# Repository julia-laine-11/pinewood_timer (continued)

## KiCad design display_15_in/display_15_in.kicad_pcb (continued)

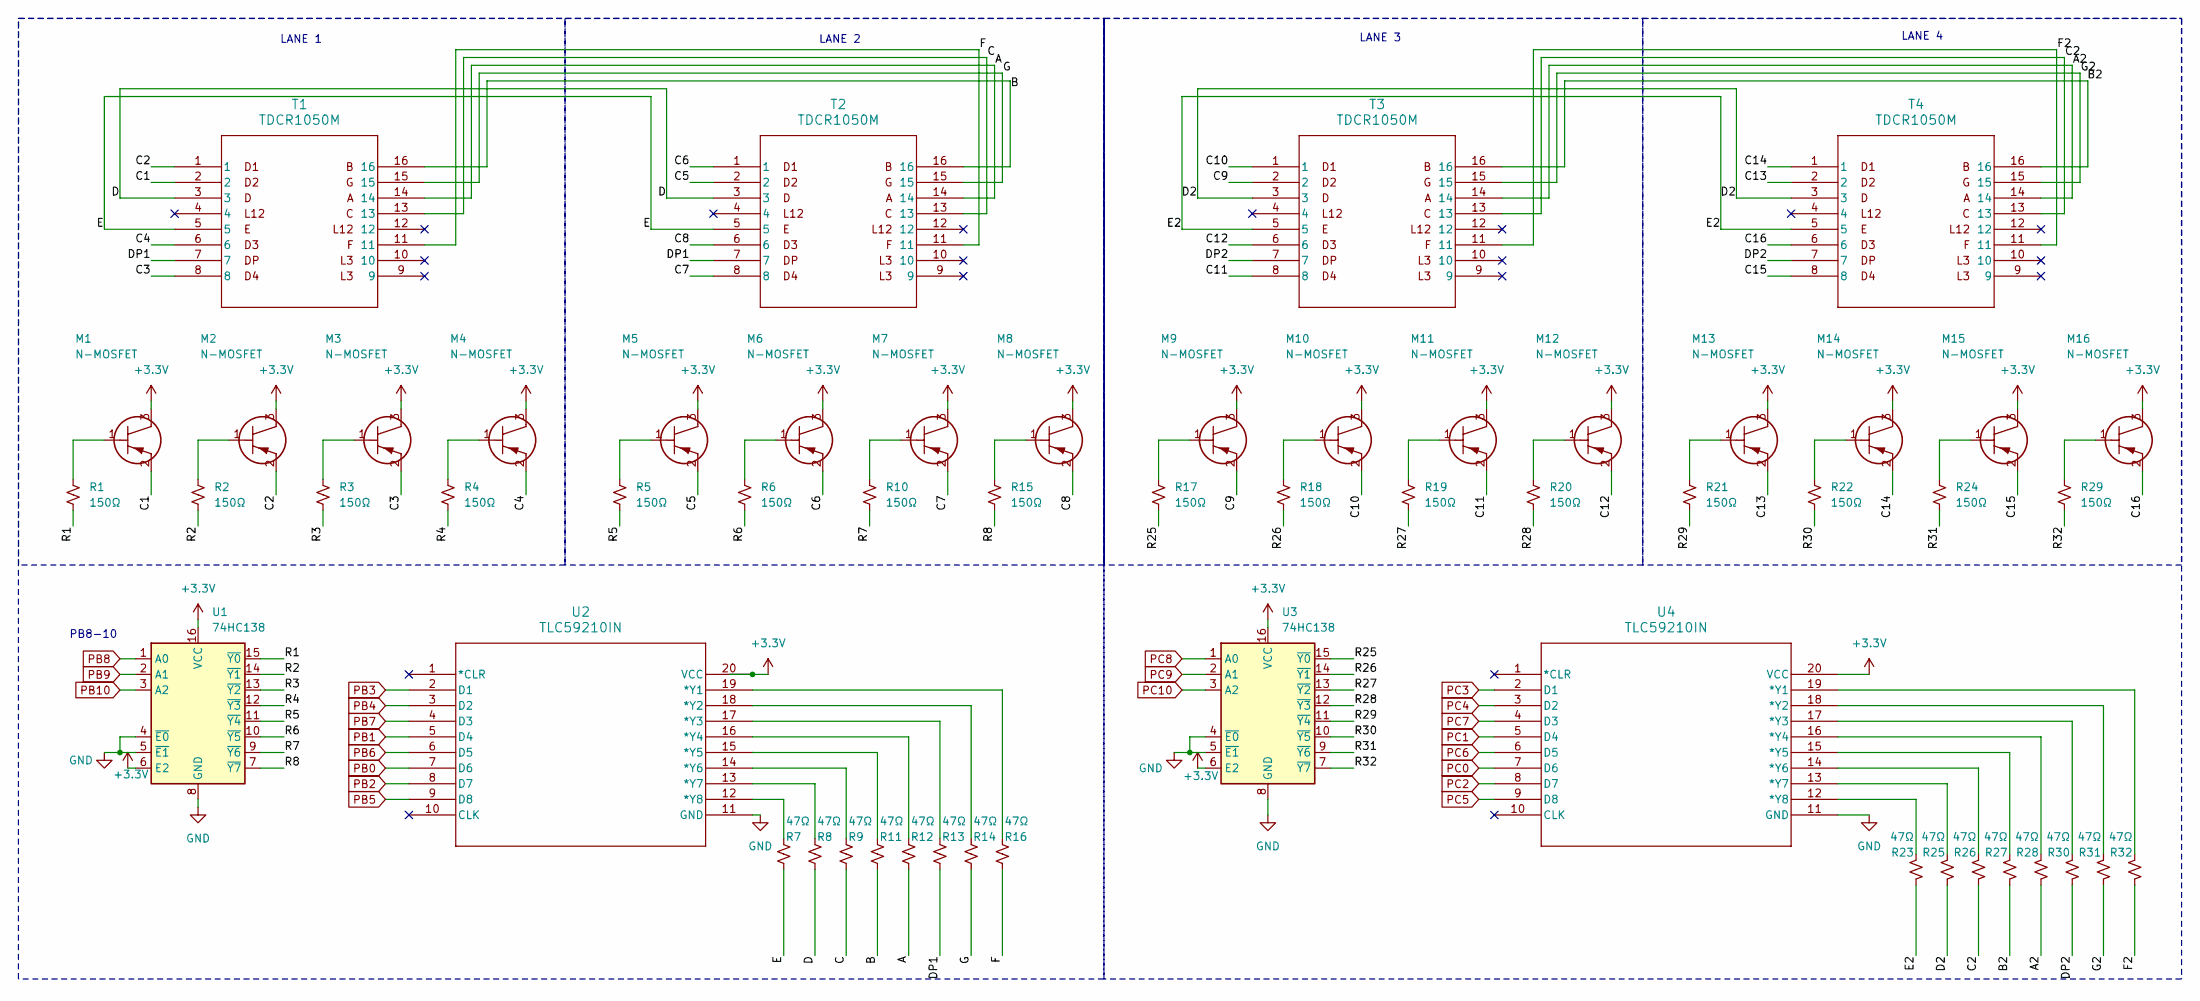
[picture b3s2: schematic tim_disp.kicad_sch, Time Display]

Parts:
M1, M2, M3, M4, M5, M6, M7, M8, M9, M10, M11, M12, M13, M14, M15, M16: N-MOSFET; TO-236AB_SOT23_NEX
R1, R2, R3, R4, R5, R6, R10, R15, R17, R18, R19, R20, R21, R22, R24, R29: 150Ω; R_0805_2012Metric
R7, R8, R9, R11, R12, R13, R14, R16, R23, R25, R26, R27, R28, R30, R31, R32: 47Ω; R_0805_2012Metric
T1, T2, T3, T4: TDCR1050M; TDCG1060M_VIS
U1, U3: 74HC138; SOIC127P600X175-16N
U2, U4: TLC59210IN; SOP65P640X120-20N

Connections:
+3.3V: M1.3, M2.3, M3.3, M4.3, M5.3, M6.3, M7.3, M8.3, M9.3, M10.3, M11.3, M12.3, M13.3, M14.3, M15.3, M16.3, U1.6 (E2), U1.16 (VCC), U2.20 (VCC), U3.6 (E2), U3.16 (VCC), U4.20 (VCC); also elsewhere on the board
/tim_disp/A: R12.2, T1.14, T2.14
/tim_disp/A2: R28.2, T3.14, T4.14
/tim_disp/B: R11.2, T1.16, T2.16
/tim_disp/B2: R27.2, T3.16, T4.16
/tim_disp/C: R9.2, T1.13, T2.13
/tim_disp/C1: M1.2, T1.2
/tim_disp/C2: M2.2, R26.2, T1.1, T3.13, T4.13
/tim_disp/C3: M3.2, T1.8
/tim_disp/C4: M4.2, T1.6
/tim_disp/C5: M5.2, T2.2
/tim_disp/C6: M6.2, T2.1
/tim_disp/C7: M7.2, T2.8
/tim_disp/C8: M8.2, T2.6
/tim_disp/C9: M9.2, T3.2
/tim_disp/C10: M10.2, T3.1
/tim_disp/C11: M11.2, T3.8
/tim_disp/C12: M12.2, T3.6
/tim_disp/C13: M13.2, T4.2
/tim_disp/C14: M14.2, T4.1
/tim_disp/C15: M15.2, T4.8
/tim_disp/C16: M16.2, T4.6
/tim_disp/D: R8.2, T1.3, T2.3
/tim_disp/D2: R25.2, T3.3, T4.3
/tim_disp/DP1: R13.2, T1.7, T2.7
/tim_disp/DP2: R30.2, T3.7, T4.7
/tim_disp/E: R7.2, T1.5, T2.5
/tim_disp/E2: R23.2, T3.5, T4.5
/tim_disp/F: R16.2, T1.11, T2.11
/tim_disp/F2: R32.2, T3.11, T4.11
/tim_disp/G: R14.2, T1.15, T2.15
/tim_disp/G2: R31.2, T3.15, T4.15
/tim_disp/R1: R1.2, U1.15 (~Y0)
/tim_disp/R2: R2.2, U1.14 (~Y1)
/tim_disp/R3: R3.2, U1.13 (~Y2)
/tim_disp/R4: R4.2, U1.12 (~Y3)
/tim_disp/R5: R5.2, U1.11 (~Y4)
/tim_disp/R6: R6.2, U1.10 (~Y5)
/tim_disp/R7: R10.2, U1.9 (~Y6)
/tim_disp/R8: R15.2, U1.7 (~Y7)
/tim_disp/R25: R17.2, U3.15 (~Y0)
/tim_disp/R26: R18.2, U3.14 (~Y1)
/tim_disp/R27: R19.2, U3.13 (~Y2)
/tim_disp/R28: R20.2, U3.12 (~Y3)
/tim_disp/R29: R21.2, U3.11 (~Y4)
/tim_disp/R30: R22.2, U3.10 (~Y5)
/tim_disp/R31: R24.2, U3.9 (~Y6)
/tim_disp/R32: R29.2, U3.7 (~Y7)
GND: U1.4 (~E0), U1.5 (~E1), U1.8 (GND), U2.11 (GND), U3.4 (~E0), U3.5 (~E1), U3.8 (GND), U4.11 (GND); also elsewhere on the board
unnamed: M1.1, R1.1
unnamed: M2.1, R2.1
unnamed: M3.1, R3.1
unnamed: M4.1, R4.1
unnamed: M5.1, R5.1
unnamed: M6.1, R6.1
unnamed: M7.1, R10.1
unnamed: M8.1, R15.1
unnamed: M9.1, R17.1
unnamed: M10.1, R18.1
unnamed: M11.1, R19.1
unnamed: M12.1, R20.1
unnamed: M13.1, R21.1
unnamed: M14.1, R22.1
unnamed: M15.1, R24.1
unnamed: M16.1, R29.1
unnamed: R16.1, U2.19 (*Y1)
unnamed: R14.1, U2.18 (*Y2)
unnamed: R13.1, U2.17 (*Y3)
unnamed: R12.1, U2.16 (*Y4)
unnamed: R11.1, U2.15 (*Y5)
unnamed: R9.1, U2.14 (*Y6)
unnamed: R8.1, U2.13 (*Y7)
unnamed: R7.1, U2.12 (*Y8)
unnamed: R32.1, U4.19 (*Y1)
unnamed: R31.1, U4.18 (*Y2)
unnamed: R30.1, U4.17 (*Y3)
unnamed: R28.1, U4.16 (*Y4)
unnamed: R27.1, U4.15 (*Y5)
unnamed: R26.1, U4.14 (*Y6)
unnamed: R25.1, U4.13 (*Y7)
unnamed: R23.1, U4.12 (*Y8)
PB0: U2.7 (D6); also elsewhere on the board
PB1: U2.5 (D4); also elsewhere on the board
PB2: U2.8 (D7); also elsewhere on the board
PB3: U2.2 (D1); also elsewhere on the board
PB4: U2.3 (D2); also elsewhere on the board
PB5: U2.9 (D8); also elsewhere on the board
PB6: U2.6 (D5); also elsewhere on the board
PB7: U2.4 (D3); also elsewhere on the board
PB8: U1.1 (A0); also elsewhere on the board
PB9: U1.2 (A1); also elsewhere on the board
PB10: U1.3 (A2); also elsewhere on the board
PC0: U4.7 (D6); also elsewhere on the board
PC1: U4.5 (D4); also elsewhere on the board
PC2: U4.8 (D7); also elsewhere on the board
PC3: U4.2 (D1); also elsewhere on the board
PC4: U4.3 (D2); also elsewhere on the board
PC5: U4.9 (D8); also elsewhere on the board
PC6: U4.6 (D5); also elsewhere on the board
PC7: U4.4 (D3); also elsewhere on the board
PC8: U3.1 (A0); also elsewhere on the board
PC9: U3.2 (A1); also elsewhere on the board
PC10: U3.3 (A2); also elsewhere on the board

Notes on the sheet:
LANE 4
LANE 2
PB8-10
LANE 1
LANE 3

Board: 2 copper layers, 78 parts (0 on the bottom side), 126 nets, no tracks yet.

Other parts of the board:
J1: 559592430; CONN24_559592430_MOL
PT1, PT2, PT3, PT4: LED_D5.0mm
R41, R42, R43, R44: 56KΩ; R_0805_2012Metric
U9: S16B-PHDSSLFSN; S16B-PHDSSLFSN_JST

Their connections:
+3.3V: J1.23, PT1.1 (+), PT2.1 (+), PT3.1 (+), PT4.1 (+); also elsewhere on the board
GND: J1.24, R41.2, R42.2, R43.2, R44.2; also elsewhere on the board
PA0: U9.1; also elsewhere on the board
PA1: U9.2; also elsewhere on the board
PA2: U9.3; also elsewhere on the board
PA3: U9.4; also elsewhere on the board
PA4: U9.5; also elsewhere on the board
PA5: U9.6; also elsewhere on the board
PA6: U9.7; also elsewhere on the board
PA7: U9.8; also elsewhere on the board
PA8: U9.9; also elsewhere on the board
PA9: U9.10; also elsewhere on the board
PA10: U9.11; also elsewhere on the board
PA11: PT1.2 (-), R41.1, U9.12
PA12: PT2.2 (-), R42.1, U9.13
PA13: PT3.2 (-), R43.1, U9.14
PA14: PT4.2 (-), R44.1, U9.15
PB0: J1.1; also elsewhere on the board
PB1: J1.2; also elsewhere on the board
PB2: J1.3; also elsewhere on the board
PB3: J1.4; also elsewhere on the board
PB4: J1.5; also elsewhere on the board
PB5: J1.6; also elsewhere on the board
PB6: J1.7; also elsewhere on the board
PB7: J1.8; also elsewhere on the board
PB8: J1.9; also elsewhere on the board
PB9: J1.10; also elsewhere on the board
PB10: J1.11; also elsewhere on the board
PC0: J1.12; also elsewhere on the board
PC1: J1.13; also elsewhere on the board
PC2: J1.14; also elsewhere on the board
PC3: J1.15; also elsewhere on the board
PC4: J1.16; also elsewhere on the board
PC5: J1.17; also elsewhere on the board
PC6: J1.18; also elsewhere on the board
PC7: J1.19; also elsewhere on the board
PC8: J1.20; also elsewhere on the board
PC9: J1.21; also elsewhere on the board
PC10: J1.22; also elsewhere on the board

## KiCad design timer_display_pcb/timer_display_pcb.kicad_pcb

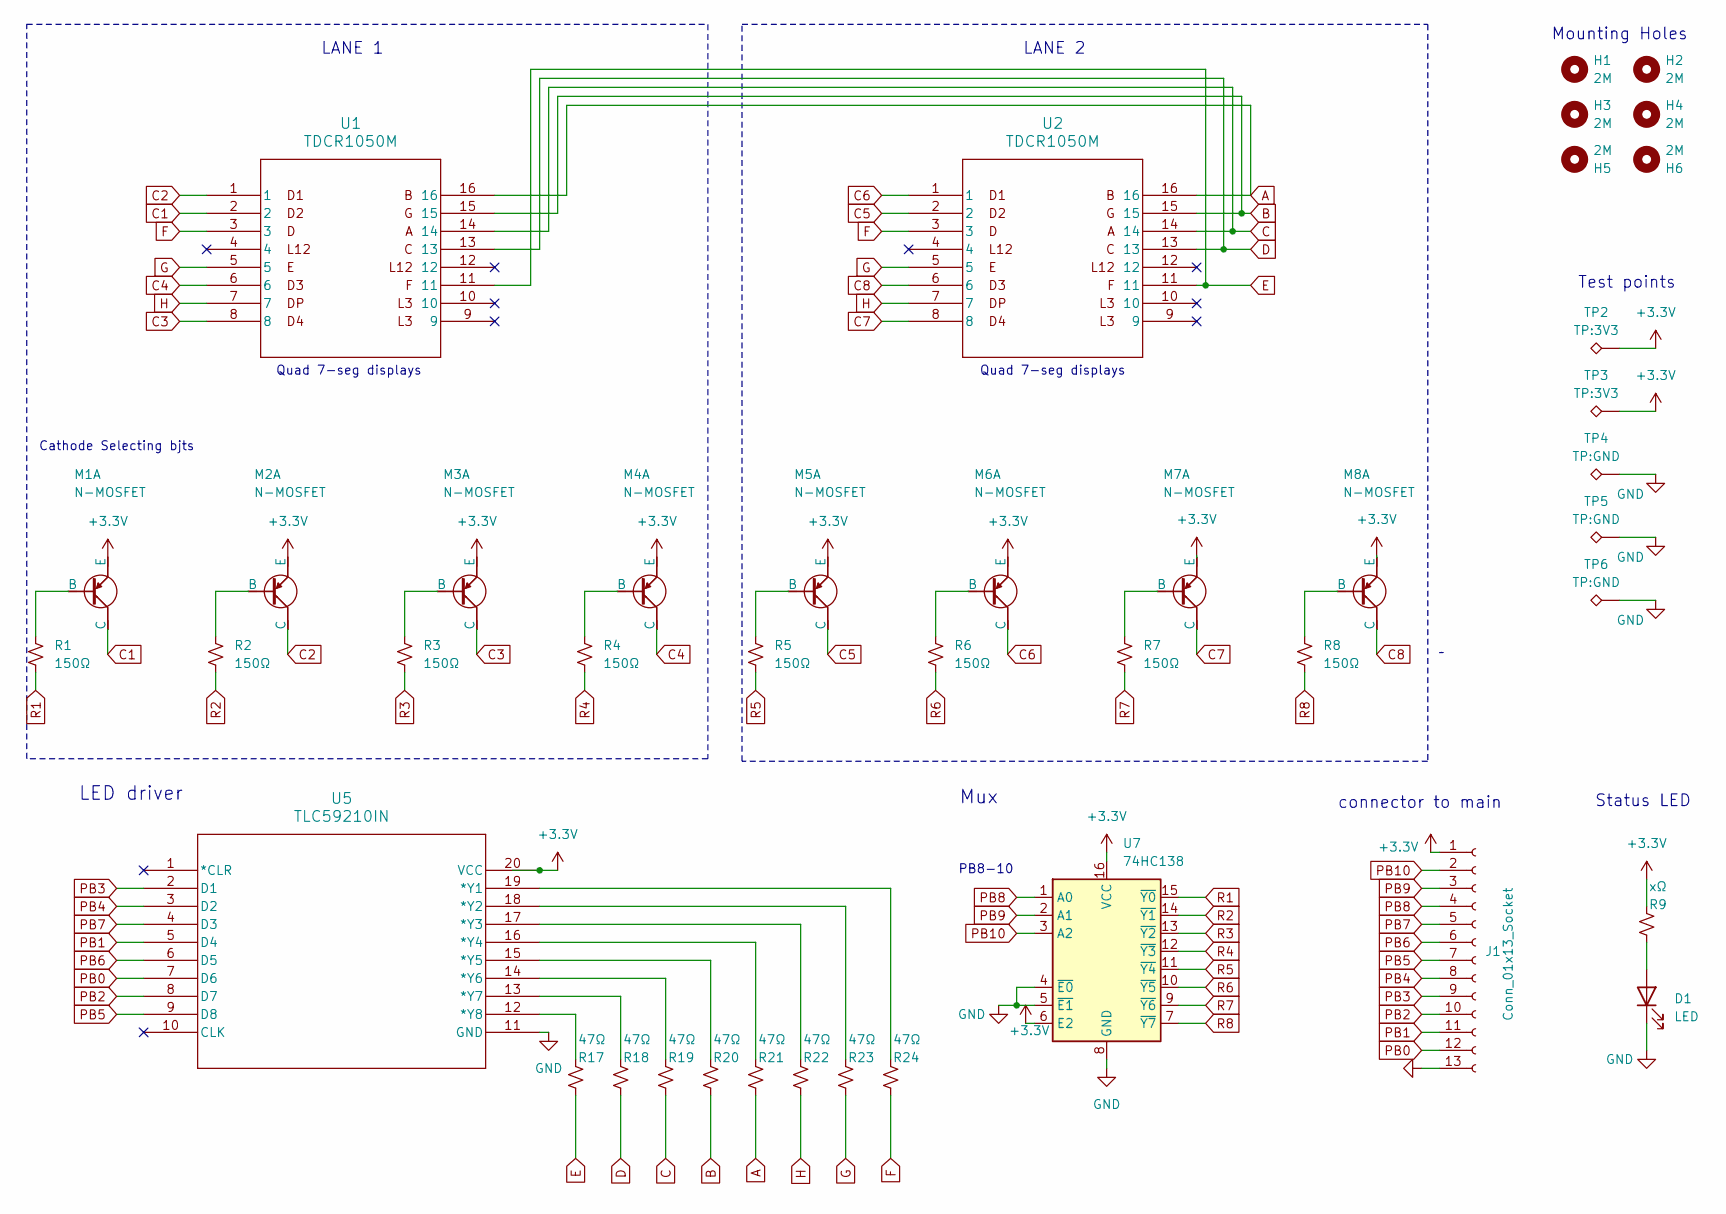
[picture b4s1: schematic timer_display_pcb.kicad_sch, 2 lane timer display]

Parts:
D1: LED; LED_0805_2012Metric
H1, H2, H3, H4, H5, H6: 2M; MountingHole_4.3mm_M4
J1: Conn_01x13_Socket; JST_EH_S13B-EH_1x13_P2.50mm_Horizontal
M1, M2, M3, M4, M5, M6, M7, M8: N-MOSFET; TO-236AB_SOT23_NEX
R1, R2, R3, R4, R5, R6, R7, R8: 150Ω; R_0805_2012Metric_Pad1.20x1.40mm_HandSolder
R9: xΩ; R_0805_2012Metric_Pad1.20x1.40mm_HandSolder
R17, R18, R19, R20, R21, R22, R23, R24: 47Ω; R_0805_2012Metric_Pad1.20x1.40mm_HandSolder
TP2, TP3: TP:3V3; TestPoint_Pad_2.0x2.0mm
TP4, TP5, TP6: TP:GND; TestPoint_Pad_2.0x2.0mm
U1, U2: TDCR1050M; TDCG1060M_VIS
U5: TLC59210IN; SOP65P640X120-20N
U7: 74HC138; SOIC127P600X175-16N

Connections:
+3.3V: J1.1, M1.1 (E), M2.1 (E), M3.1 (E), M4.1 (E), M5.1 (E), M6.1 (E), M7.1 (E), M8.1 (E), R9.1, TP2.1, TP3.1, U5.20 (VCC), U7.6 (E2), U7.16 (VCC)
A: R21.2, U1.16, U2.16
B: R20.2, U1.15, U2.15
C: R19.2, U1.14, U2.14
C1: M1.3 (C), U1.2
C2: M2.3 (C), U1.1
C3: M3.3 (C), U1.8
C4: M4.3 (C), U1.6
C5: M5.3 (C), U2.2
C6: M6.3 (C), U2.1
C7: M7.3 (C), U2.8
C8: M8.3 (C), U2.6
D: R18.2, U1.13, U2.13
E: R17.2, U1.11, U2.11
F: R24.2, U1.3, U2.3
G: R23.2, U1.5, U2.5
GND: D1.1 (K), J1.13, TP4.1, TP5.1, TP6.1, U5.11 (GND), U7.4 (~E0), U7.5 (~E1), U7.8 (GND)
H: R22.2, U1.7, U2.7
unnamed: D1.2 (A), R9.2
unnamed: M1.2 (B), R1.1
unnamed: M2.2 (B), R2.1
unnamed: M3.2 (B), R3.1
unnamed: M4.2 (B), R4.1
unnamed: M5.2 (B), R5.1
unnamed: M6.2 (B), R6.1
unnamed: M7.2 (B), R7.1
unnamed: M8.2 (B), R8.1
unnamed: R24.1, U5.19 (*Y1)
unnamed: R23.1, U5.18 (*Y2)
unnamed: R22.1, U5.17 (*Y3)
unnamed: R21.1, U5.16 (*Y4)
unnamed: R20.1, U5.15 (*Y5)
unnamed: R19.1, U5.14 (*Y6)
unnamed: R18.1, U5.13 (*Y7)
unnamed: R17.1, U5.12 (*Y8)
PB0: J1.12, U5.7 (D6)
PB1: J1.11, U5.5 (D4)
PB2: J1.10, U5.8 (D7)
PB3: J1.9, U5.2 (D1)
PB4: J1.8, U5.3 (D2)
PB5: J1.7, U5.9 (D8)
PB6: J1.6, U5.6 (D5)
PB7: J1.5, U5.4 (D3)
PB8: J1.4, U7.1 (A0)
PB9: J1.3, U7.2 (A1)
PB10: J1.2, U7.3 (A2)
R1: R1.2, U7.15 (~Y0)
R2: R2.2, U7.14 (~Y1)
R3: R3.2, U7.13 (~Y2)
R4: R4.2, U7.12 (~Y3)
R5: R5.2, U7.11 (~Y4)
R6: R6.2, U7.10 (~Y5)
R7: R7.2, U7.9 (~Y6)
R8: R8.2, U7.7 (~Y7)

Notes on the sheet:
LANE 1
LANE 2
connector to main
Cathode Selecting bjts
PB8-10
Quad 7-seg displays
Status LED
Test points
LED driver
Mounting Holes
Mux

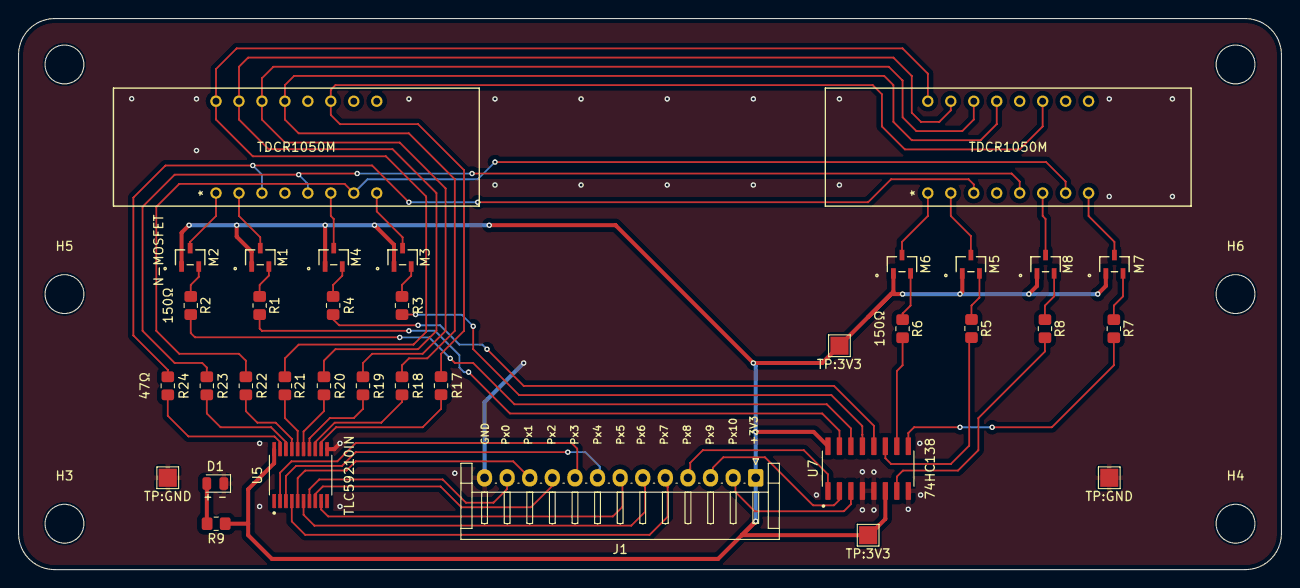
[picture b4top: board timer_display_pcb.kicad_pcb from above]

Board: 2 copper layers, 139.7 x 61.0 mm, 42 parts (1 on the bottom side), 54 nets.

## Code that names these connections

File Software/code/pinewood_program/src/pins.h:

#ifndef PINEWOOD_PINS_H
#define PINEWOOD_PINS_H

#include "stm32f0xx.h"
#include <stdint.h>

/*
 * ============================================================================
 *  Pinewood Derby Timer — GPIO map (STM32F091RCT6)
 * ============================================================================
 *
 *  All pin names refer to the MCU package pin function.
 *  Hex masks are bit positions in the port ODR/IDR/BSRR (bit N = PN).
 *
 *  Display data uses TLC59211 parallel inputs D1-D8 (port bits 0-7) plus
 *  74HC138 mux address A0-A2 (port bits 8-10).  Eleven pins per bank.
 *
 *  See INDEX.md and README2.md for full software documentation.
 * ============================================================================
 */

#define NUM_LANES 4

/* -------------------------------------------------------------------------- */
/*  Placement display — GPIOA PA0 .. PA10 (11 pins)                           */
/* -------------------------------------------------------------------------- */
#define PLACEMENT_PORT GPIOA

/* Bits PA0-PA10 enabled: 0x07FF */
#define DISPLAY_PIN_MASK 0x07FFU /* PA0=bit0 .. PA10=bit10 */

/* PA0  — TLC59211 D1 / segment bus bit 0 */
/* PA1  — TLC59211 D2 / segment bus bit 1 */
/* PA2  — TLC59211 D3 / segment bus bit 2 */
/* PA3  — TLC59211 D4 / segment bus bit 3 */
/* PA4  — TLC59211 D5 / segment bus bit 4 */
/* PA5  — TLC59211 D6 / segment bus bit 5 */
/* PA6  — TLC59211 D7 / segment bus bit 6 */
/* PA7  — TLC59211 D8 / segment bus bit 7 */
/* PA8  — 74HC138 A0 (mux bit 0) */
/* PA9  — 74HC138 A1 (mux bit 1) */
/* PA10 — 74HC138 A2 (mux bit 2) */

/* -------------------------------------------------------------------------- */
/*  Timer display lanes 1 & 2 — GPIOB PB0 .. PB10                             */
/* -------------------------------------------------------------------------- */
#define TIMER_L12_PORT GPIOB

/* PB0  — TLC59211 D1 / segment bus bit 0 */
/* PB1  — TLC59211 D2 */
/* PB2  — TLC59211 D3 */
/* PB3  — TLC59211 D4 */
/* PB4  — TLC59211 D5 */
/* PB5  — TLC59211 D6 */
/* PB6  — TLC59211 D7 */
/* PB7  — TLC59211 D8 */
/* PB8  — 74HC138 A0 (mux bit 0) */
/* PB9  — 74HC138 A1 (mux bit 1) */
/* PB10 — 74HC138 A2 (mux bit 2) */

/* -------------------------------------------------------------------------- */
/*  Timer display lanes 3 & 4 — GPIOC PC0 .. PC10                             */
/* -------------------------------------------------------------------------- */
#define TIMER_L34_PORT GPIOC

/* PC0  — TLC59211 D1 / segment bus bit 0 */
/* PC1  — TLC59211 D2 */
/* PC2  — TLC59211 D3 */
/* PC3  — TLC59211 D4 */
/* PC4  — TLC59211 D5 */
/* PC5  — TLC59211 D6 */
/* PC6  — TLC59211 D7 */
/* PC7  — TLC59211 D8 */
/* PC8  — 74HC138 A0 (mux bit 0) */
/* PC9  — 74HC138 A1 (mux bit 1) */
/* PC10 — 74HC138 A2 (mux bit 2) */

/* -------------------------------------------------------------------------- */
/*  Race control inputs                                                         */
/* -------------------------------------------------------------------------- */

/* PC11 — start lever / release switch, mask 0x0800 (bit 11) */
#define START_PORT     GPIOC
#define START_PIN_MASK (1U << 11) /* PC11, 0x0800 */

/*
 * PA15 — reset button (placeholder until mainboard routing is final).
 * Mask 0x8000 (bit 15).  PC12 is reserved for UART5_TX.
 */
#define RESET_PORT     GPIOA
#define RESET_PIN_MASK (1U << 15) /* PA15, 0x8000 */

/* Finish-line IR receivers — GPIOB PB11 .. PB14, one per lane */
#define FINISH_PORT GPIOB

#define FINISH_LANE_MASK(lane) (1U << (11 + (lane)))
/* Lane 1: PB11  0x0800  (bit 11) */
/* Lane 2: PB12  0x1000  (bit 12) */
/* Lane 3: PB13  0x2000  (bit 13) */
/* Lane 4: PB14  0x4000  (bit 14) */

/* -------------------------------------------------------------------------- */
/*  UART5 — FT232RL USB-TTL (not used as GPIO)                                 */
/* -------------------------------------------------------------------------- */
/* PC12 — USART5_TX, AF2, mask 0x1000 (bit 12) — see uart.c */
/* PD2  — USART5_RX, AF2, mask 0x0004 (bit 2)  — see uart.c */

/* -------------------------------------------------------------------------- */
/*  Status LEDs on mainboard — GPIOC PC13 .. PC15, active high                */
/* -------------------------------------------------------------------------- */
#define LED_READY_PORT    GPIOC
#define LED_RUNNING_PORT  GPIOC
#define LED_FINISHED_PORT GPIOC

#define LED_READY_PIN    (1U << 13) /* PC13, 0x2000 */
#define LED_RUNNING_PIN  (1U << 14) /* PC14, 0x4000 */
#define LED_FINISHED_PIN (1U << 15) /* PC15, 0x8000 */

/* -------------------------------------------------------------------------- */
/*  Sensor polarity (change if hardware inverts)                              */
/* -------------------------------------------------------------------------- */
/* 1 = pressed / beam-broken reads logic high.  0 = active low. */
#define BUTTON_ACTIVE_HIGH        1
#define FINISH_SENSOR_ACTIVE_HIGH 1

/* -------------------------------------------------------------------------- */
/*  Display mux helpers                                                       */
/* -------------------------------------------------------------------------- */

/* Shift digit index (0-7) onto mux pins PA8/PB8/PC8 .. PA10/PB10/PC10. */
#define MUX_ADDR(digit) (((uint32_t)(digit) & 0x07U) << 8)

/*
 * Full ODR patterns for each lane (segment + mux preset from bring-up).
 * Decimal values from original notes: 380, 580, 680, 700.
 */
static inline uint16_t lane12_mux_addr(uint8_t lane, uint8_t digit)
{
    static const uint16_t lane_base[2] = {
        0x017CU, /* 380 dec — lane 1, PB2-PB8 pattern */
        0x0244U  /* 580 dec — lane 2 */
    };
    return (uint16_t)(lane_base[lane & 1U] + MUX_ADDR(digit));
}

static inline uint16_t lane34_mux_addr(uint8_t lane, uint8_t digit)
{
    static const uint16_t lane_base[2] = {
        0x02A8U, /* 680 dec — lane 3 */
        0x02BCU  /* 700 dec — lane 4 */
    };
    return (uint16_t)(lane_base[lane & 1U] + MUX_ADDR(digit));
}

static inline uint16_t placement_mux_addr(uint8_t lane)
{
    static const uint16_t lane_mux[4] = {
        0x017CU, /* 380 — placement lane 1, PA2-PA8 */
        0x0244U, /* 580 — placement lane 2 */
        0x02A8U, /* 680 — placement lane 3 */
        0x02BCU  /* 700 — placement lane 4 */
    };
    return lane_mux[lane];
}

#endif

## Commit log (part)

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2025-04-30 added files
2025-05-01 began schematic
2025-05-01 did some more work on the time displays
    pb and pa maybe or pc. pa might need to be adc if i cant just transistor/relay it or something
2025-05-01 worked on schematic more
2025-05-01 updated bom
2025-05-01 edited schematic
    added descriptions to sheets
    chose sensor pins
    added missing items to bom
2025-05-05 added pins
2025-06-07 worked on the ir sensors and placement display
2025-06-07 edited placement timer schematic since i can never make up my mind
2025-06-16 keep forgetting ot push - a lot of updates
    fixed stm pinout. needs a lot more support than i was providing
2025-06-18 Update README.md
    my excel doesnt let me edit :(
2025-06-18 Update README.md
    changed mux
2025-06-19 finished 2 lane display pcb
2025-07-08 Create schematics.md
    added 2 lane tmr dsp
2025-07-10 reorg
2025-07-10 added eot file
2025-07-12 edited schematic.
    realized that mux and led driver only saved me 1 pin and added a lot of extra nonsense
2025-07-12 made some test code for placement display
2025-07-13 added full end of track display board
2025-07-14 edited layout
2025-07-14 removed files
2025-07-15 more work on pcb
    finished house season 2 and made decent progress (i think) on the pcb. if it is bad ill see tomorrow lol
2025-07-15 added functions to build onto
2025-07-19 routed more traces
2025-07-20 added more traces lowkey sufferig
2025-07-20 made it less disastrous
2025-07-22 avoiding doing the via calculations or at least researching how to do them so i just added silkscreen stuff
2025-07-26 power traces, gnd plane vias, and test points
2025-07-27 began work on mainboard
    mostly schematic but i did assign footprints (if you even consider that to be working on the pcb)
    power in from usb and ONLY power from usb - no dp just vbus and gnd. still dnt know what cc or shield is but i can figure that out later
    jtag and usb-ttl for programming. will not be powered by usb while programmed.
2025-07-27 Update README.md
    updated images
2025-07-27 updated mainboard schematic
    organization and power
2025-07-27 forgor race reset button
    theres a reset on the board and a reset on the side for them to hit to clear it for the next race
2025-07-27 clear autosaved
2025-08-03 updated schematic
    added:
    -footprints
    -status leds
    -libraries
    -connectors
    separated into sheets since too many components on pange
2025-08-03 pushing for the evening
    didnt add much, just moved things around and fixed footprints
2025-08-04 Lowkey forgot the start switch so i added that
2025-08-05 layout
    worked on the layput but im actively falling asleep while working on it so im going to call it a day
2025-08-05 add layer
2025-08-06 routed traces
2025-08-06 Rename pinewoodBOM.xlsx to materials_to_buy/pinewoodBOM.xlsx
2025-08-06 cleanup
2025-08-06 display and design rules
2025-08-06 added libraries
2025-08-06 gitignore fixed finally
2025-08-06 cleanup again
    a lot of old unused files in the way
2025-08-07 lowkey accidentally deleted everything but i brought a previous commit back since i am a true girlboss
    like i deleted inner layers since i thought iw as looking at a diff board
2025-08-07 final push for the night
2025-08-07 fixed schematic pcb agreement errors
2025-08-08 generated gbr files
2025-08-13 gbr files
    ordered pcbs
2025-08-13 enable ports
    setup pin config
2025-08-13 IDR
    made masks then got distracted lowkey
2025-09-18 testing new git form + fixed funny ground wire
2025-09-18 fixed what i messed up just now
2026-06-22 Update README
    we back at it
2026-06-22 i let the robot loose
    once i get my programming cables ill test it. i have never tried this before so well see how well it does
    i need to remake the board as well. usbc for easy compatibility would be nice
